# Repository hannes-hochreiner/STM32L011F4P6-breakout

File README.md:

# STM32L011F4P6-breakout
Simple breakout board for the STM32L011F4P6

## Flash test
I tested flashing the breakout using a raspberry pi and OpenOCD.
For installing OpenOCD, I followed the tutorial on [adafruit.com](https://learn.adafruit.com/programming-microcontrollers-using-openocd-on-raspberry-pi/compiling-openocd).
I used the following configuration:
```
source [find interface/raspberrypi-native.cfg]
transport select swd
source [find target/stm32l0.cfg]
bcm2835gpio_swd_nums 25 24
bcm2835gpio_trst_num 7
bcm2835gpio_srst_num 18
reset_config srst_nogate

adapter_nsrst_delay 100
adapter_nsrst_assert_width 100

init
targets
reset halt
```
I started OpenOCD with the configuration...
```
sudo openocd -f stm32.cfg
```
...and connected through telnet to it...
```
telnet localhost 4444
```
I then flashed a small test program:
```
program stmTest.hex verify reset
```

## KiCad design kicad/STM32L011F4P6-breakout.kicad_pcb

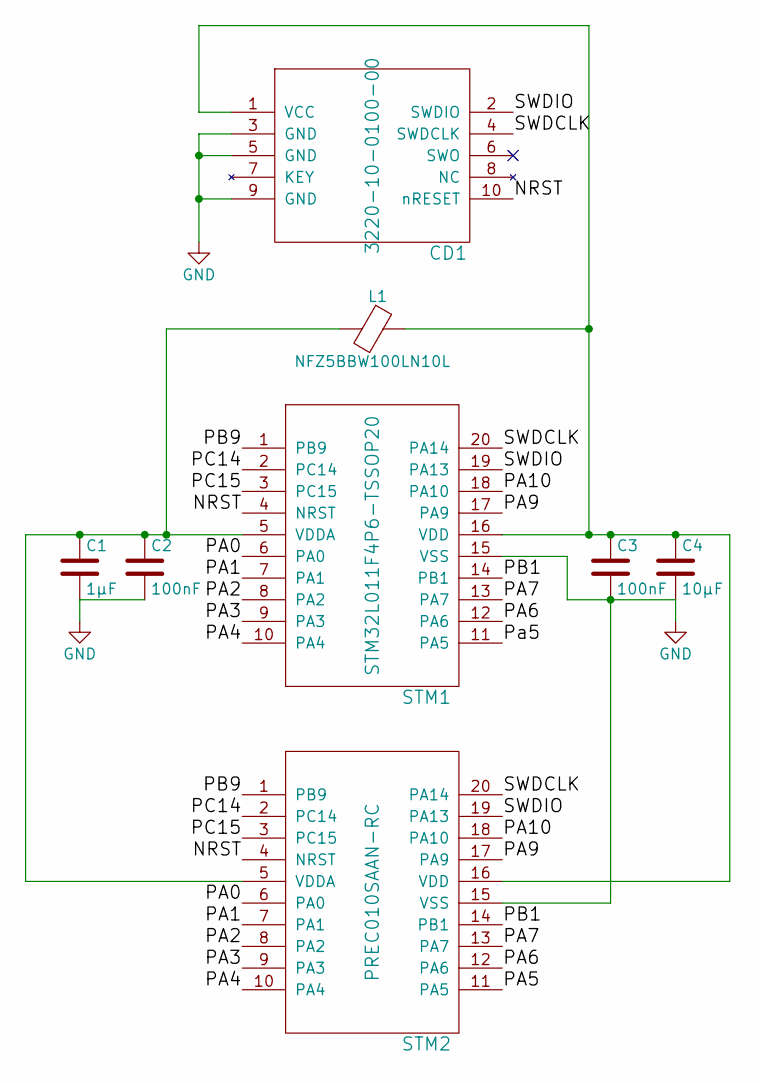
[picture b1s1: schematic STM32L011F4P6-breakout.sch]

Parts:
C1: 1µF; C_0603_HandSoldering
C2, C3: 100nF; C_0603_HandSoldering
C4: 10µF; C_0603_HandSoldering
CD1: 3220-10-0100-00; CORTEX-DEBUG
L1: NFZ5BBW100LN10L; C_2220_HandSoldering
STM1: STM32L011F4P6-TSSOP20; TSSOP-20_4.4x6.5mm_Pitch0.65mm
STM2: PREC010SAAN-RC; STM32CONN

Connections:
/NRST: CD1.10 (nRESET), STM1.4 (NRST), STM2.4 (NRST)
/PA0: STM1.6 (PA0), STM2.6 (PA0)
/PA1: STM1.7 (PA1), STM2.7 (PA1)
/PA2: STM1.8 (PA2), STM2.8 (PA2)
/PA3: STM1.9 (PA3), STM2.9 (PA3)
/PA4: STM1.10 (PA4), STM2.10 (PA4)
/PA5: STM1.11 (PA5), STM2.11 (PA5)
/PA6: STM1.12 (PA6), STM2.12 (PA6)
/PA7: STM1.13 (PA7), STM2.13 (PA7)
/PA9: STM1.17 (PA9), STM2.17 (PA9)
/PA10: STM1.18 (PA10), STM2.18 (PA10)
/PB1: STM1.14 (PB1), STM2.14 (PB1)
/PB9: STM1.1 (PB9), STM2.1 (PB9)
/PC14: STM1.2 (PC14), STM2.2 (PC14)
/PC15: STM1.3 (PC15), STM2.3 (PC15)
/SWDCLK: CD1.4 (SWDCLK), STM1.20 (PA14), STM2.20 (PA14)
/SWDIO: CD1.2 (SWDIO), STM1.19 (PA13), STM2.19 (PA13)
GND: C1.2, C2.2, C3.2, C4.2, CD1.3 (GND), CD1.5 (GND), CD1.9 (GND), STM1.15 (VSS), STM2.15 (VSS)
unnamed: C1.1, C2.1, L1.2, STM1.5 (VDDA), STM2.5 (VDDA)
unnamed: C3.1, C4.1, CD1.1 (VCC), L1.1, STM1.16 (VDD), STM2.16 (VDD)

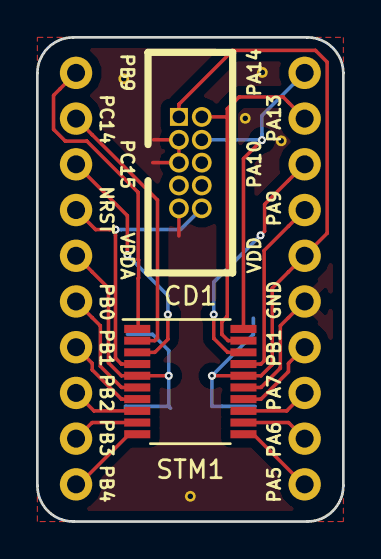
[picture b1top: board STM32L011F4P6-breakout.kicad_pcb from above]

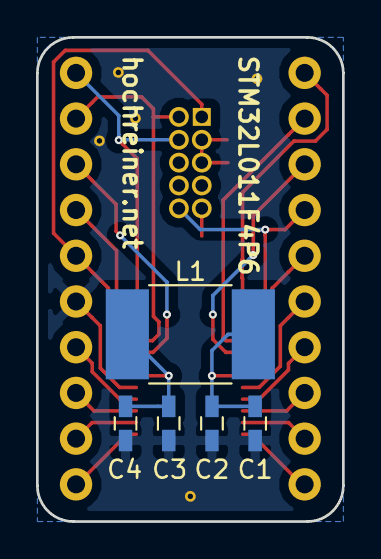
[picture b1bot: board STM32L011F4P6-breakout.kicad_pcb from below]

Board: 2 copper layers, 17.0 x 26.9 mm, 8 parts (5 on the bottom side), 20 nets.

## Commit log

2017-09-27 first snapshot
2017-09-27 snapshot
2017-12-02 moved STM down and rotated debug connector
2018-01-22 aligned footprints and added pin labels
2018-01-22 increased board margin by moving a trace closer to the pins
2018-01-23 re-aligned pin labels
2018-01-24 changed ferrite bead
2018-02-14 description of flash test
